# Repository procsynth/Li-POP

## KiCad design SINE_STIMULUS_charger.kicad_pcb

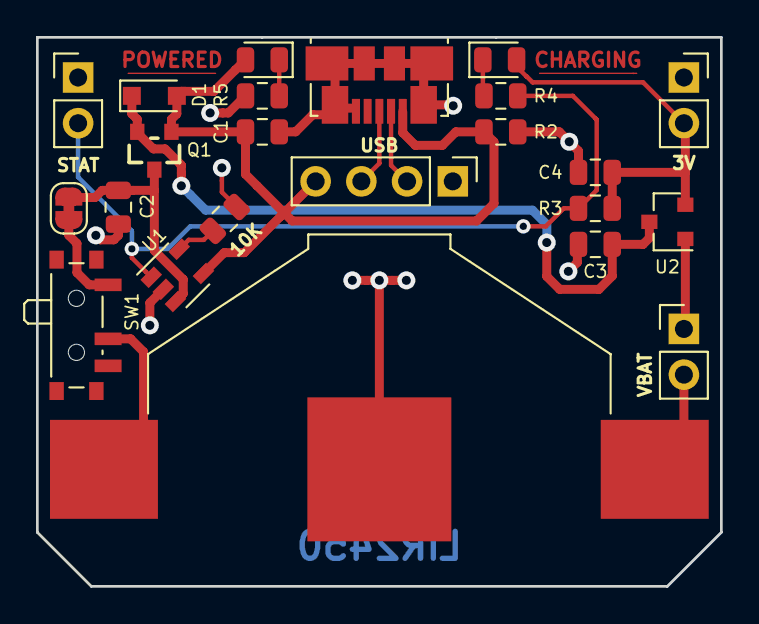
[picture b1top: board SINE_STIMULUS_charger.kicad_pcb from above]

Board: 2 copper layers, 38.0 x 30.5 mm, 23 parts (0 on the bottom side), 13 nets.

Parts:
BT1: Battery; BatteryHolder_Keystone_3008_1x2450
C1, C2, C3: 4.7µF; C_0805_2012Metric
C4: 1µF; C_0805_2012Metric
D1: BAT60JFILM; D_SOD-323_HandSoldering
D2: CHARGING; LED_0805_2012Metric
D3: ON; LED_0805_2012Metric
J1: USB_B_Micro; USB_Micro-B_Molex_47346-0001
J2: USB_BO; PinHeader_1x04_P2.54mm_Vertical
J3: 3V; PinSocket_1x02_P2.54mm_Vertical
JP1: Current test point; SolderJumper-2_P1.3mm_Bridged_RoundedPad1.0x1.5mm
Q1: DMP1045U; SOT23_FET
R1: 10K; R_0805_2012Metric
R2: 100K; R_0805_2012Metric
R3: 47K; R_0805_2012Metric
R4: 300; R_0805_2012Metric
R5: 470R; R_0805_2012Metric
SW1: POWER; SW_SPDT_PCM12
TP1: VBAT; PinHeader_1x02_P2.54mm_Vertical
TP2: STAT; PinHeader_1x02_P2.54mm_Vertical
U1: MCP73831-2-OT; SOT-23-5
U2: MCP1700-3002E_SOT23; SOT-23

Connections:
/Power Management/LIPO_IN: JP1.1, SW1.1
/Power Management/V_UNREG: C3.1, D1.1, Q1.3, U2.3
/STAT: R3.2, R4.2, TP2.2, U1.1
/V_LIPO: BT1.1, SW1.2, TP1.2
/V_OUT: C4.1, D2.2, J3.2, R3.1, U2.2
/V_USB: C1.1, D1.2, D3.2, J1.1, J2.4, Q1.2, R2.1, U1.4
GND: BT1.2, C1.2, C2.2, C3.2, C4.2, J1.5, J1.6, J2.1, J3.1, R1.2, R2.2, R5.2, TP1.1, TP2.1, U1.2, U2.1
unnamed: C2.1, JP1.2, Q1.1, U1.3
unnamed: D2.1, R4.1
unnamed: D3.1, R5.1
unnamed: J1.2, J2.2
unnamed: J1.3, J2.3
unnamed: R1.1, U1.5

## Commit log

2019-02-28 Empty Kicad Project
2019-03-01 Add .gitignore
2019-03-01 Add REV 1 of CHARGER test board
2019-03-01 Add README.md
2019-03-01 Change plot options
2019-03-01 Add LICENCE
